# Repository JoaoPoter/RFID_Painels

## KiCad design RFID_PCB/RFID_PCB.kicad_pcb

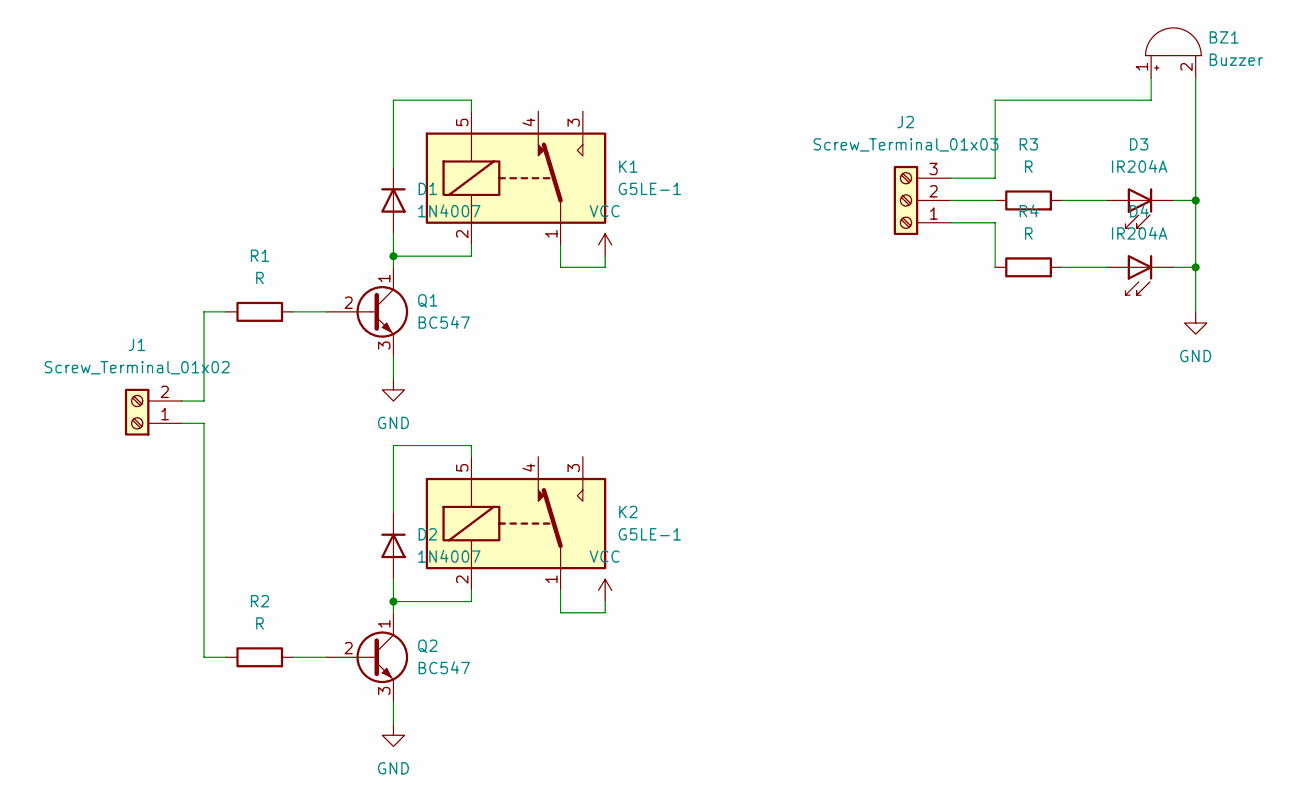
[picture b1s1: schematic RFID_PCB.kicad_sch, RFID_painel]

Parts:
BZ1: Buzzer; Buzzer_12x9.5RM7.6
D1, D2: 1N4007; D_DO-41_SOD81_P10.16mm_Horizontal
D3, D4: IR204A; LED_D3.0mm_IRBlack
J1: Screw_Terminal_01x02; PhoenixContact_MSTBA_2,5_2-G-5,08_1x02_P5.08mm_Horizontal
J2: Screw_Terminal_01x03; PhoenixContact_MSTBA_2,5_3-G-5,08_1x03_P5.08mm_Horizontal
K1, K2: G5LE-1; Relay_SPDT_Omron-G5LE-1
Q1, Q2: BC547; TO-92_Inline
R1, R2, R3, R4: R; R_Axial_DIN0204_L3.6mm_D1.6mm_P1.90mm_Vertical

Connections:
GND: BZ1.2 (+), D3.1 (K), D4.1 (K), Q1.3 (E), Q2.3 (E)
unnamed: BZ1.1 (-), J2.3
unnamed: D1.2 (A), K1.2, Q1.1 (C)
unnamed: D1.1 (K), K1.5
unnamed: D2.2 (A), K2.2, Q2.1 (C)
unnamed: D2.1 (K), K2.5
unnamed: D3.2 (A), R3.2
unnamed: D4.2 (A), R4.2
unnamed: J1.1, R2.1
unnamed: J1.2, R1.1
unnamed: J2.1, R4.1
unnamed: J2.2, R3.1
unnamed: Q1.2 (B), R1.2
unnamed: Q2.2 (B), R2.2
VCC: K1.1, K2.1

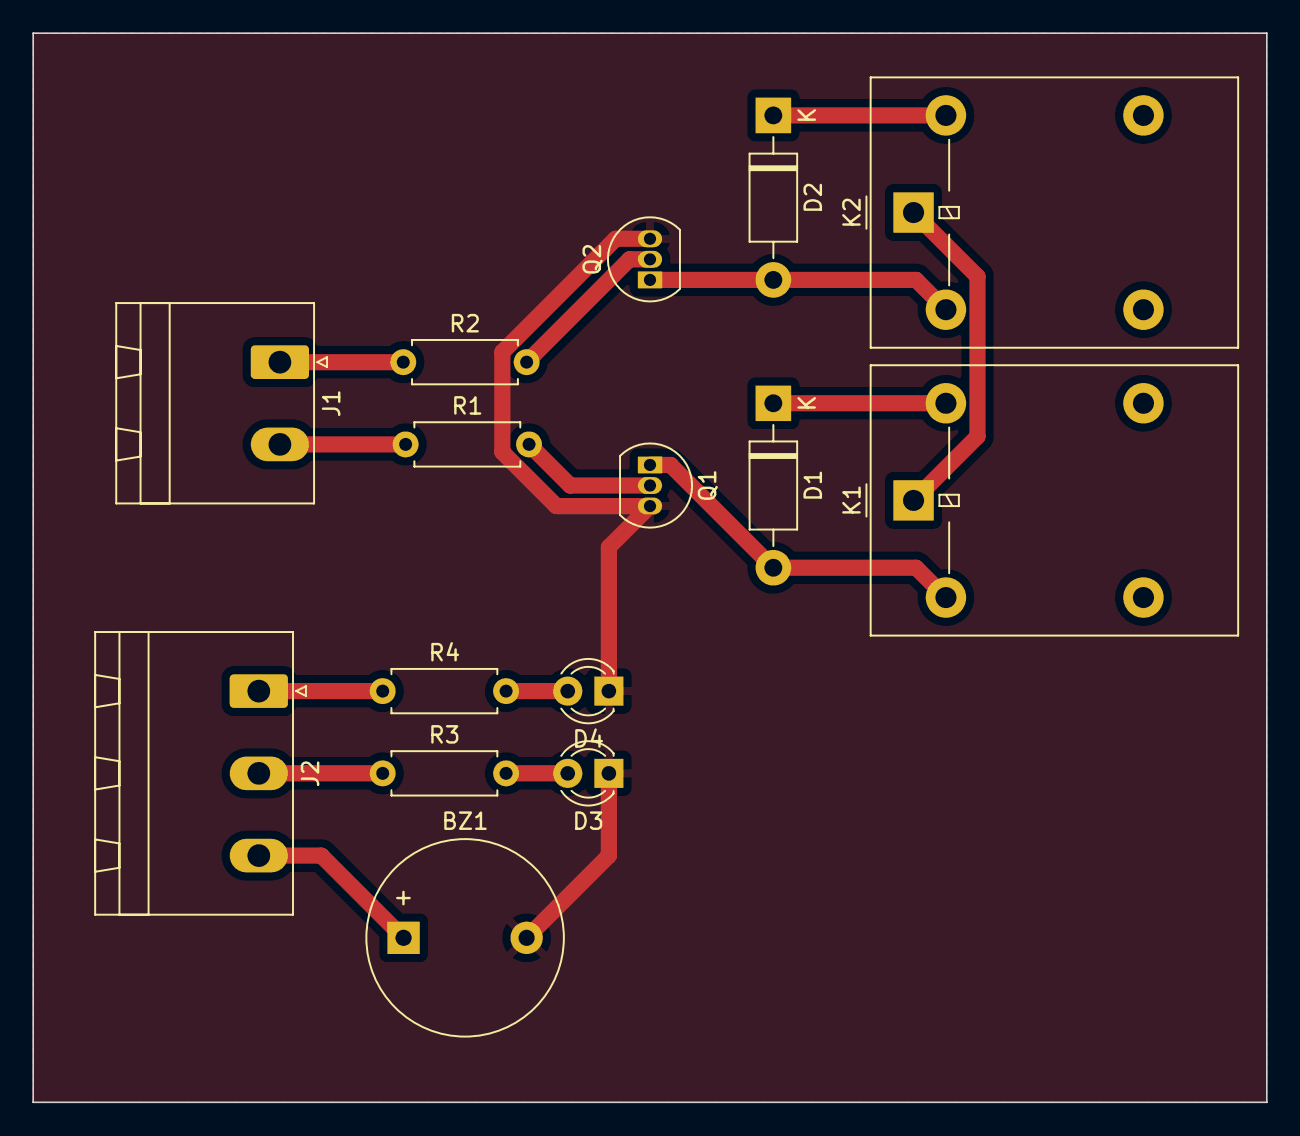
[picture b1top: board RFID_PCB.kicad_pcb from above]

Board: 2 copper layers, 76.2 x 66.0 mm, 15 parts (0 on the bottom side), 15 nets.

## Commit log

2023-09-18 RIFD_Files_KiCad_v0.1
